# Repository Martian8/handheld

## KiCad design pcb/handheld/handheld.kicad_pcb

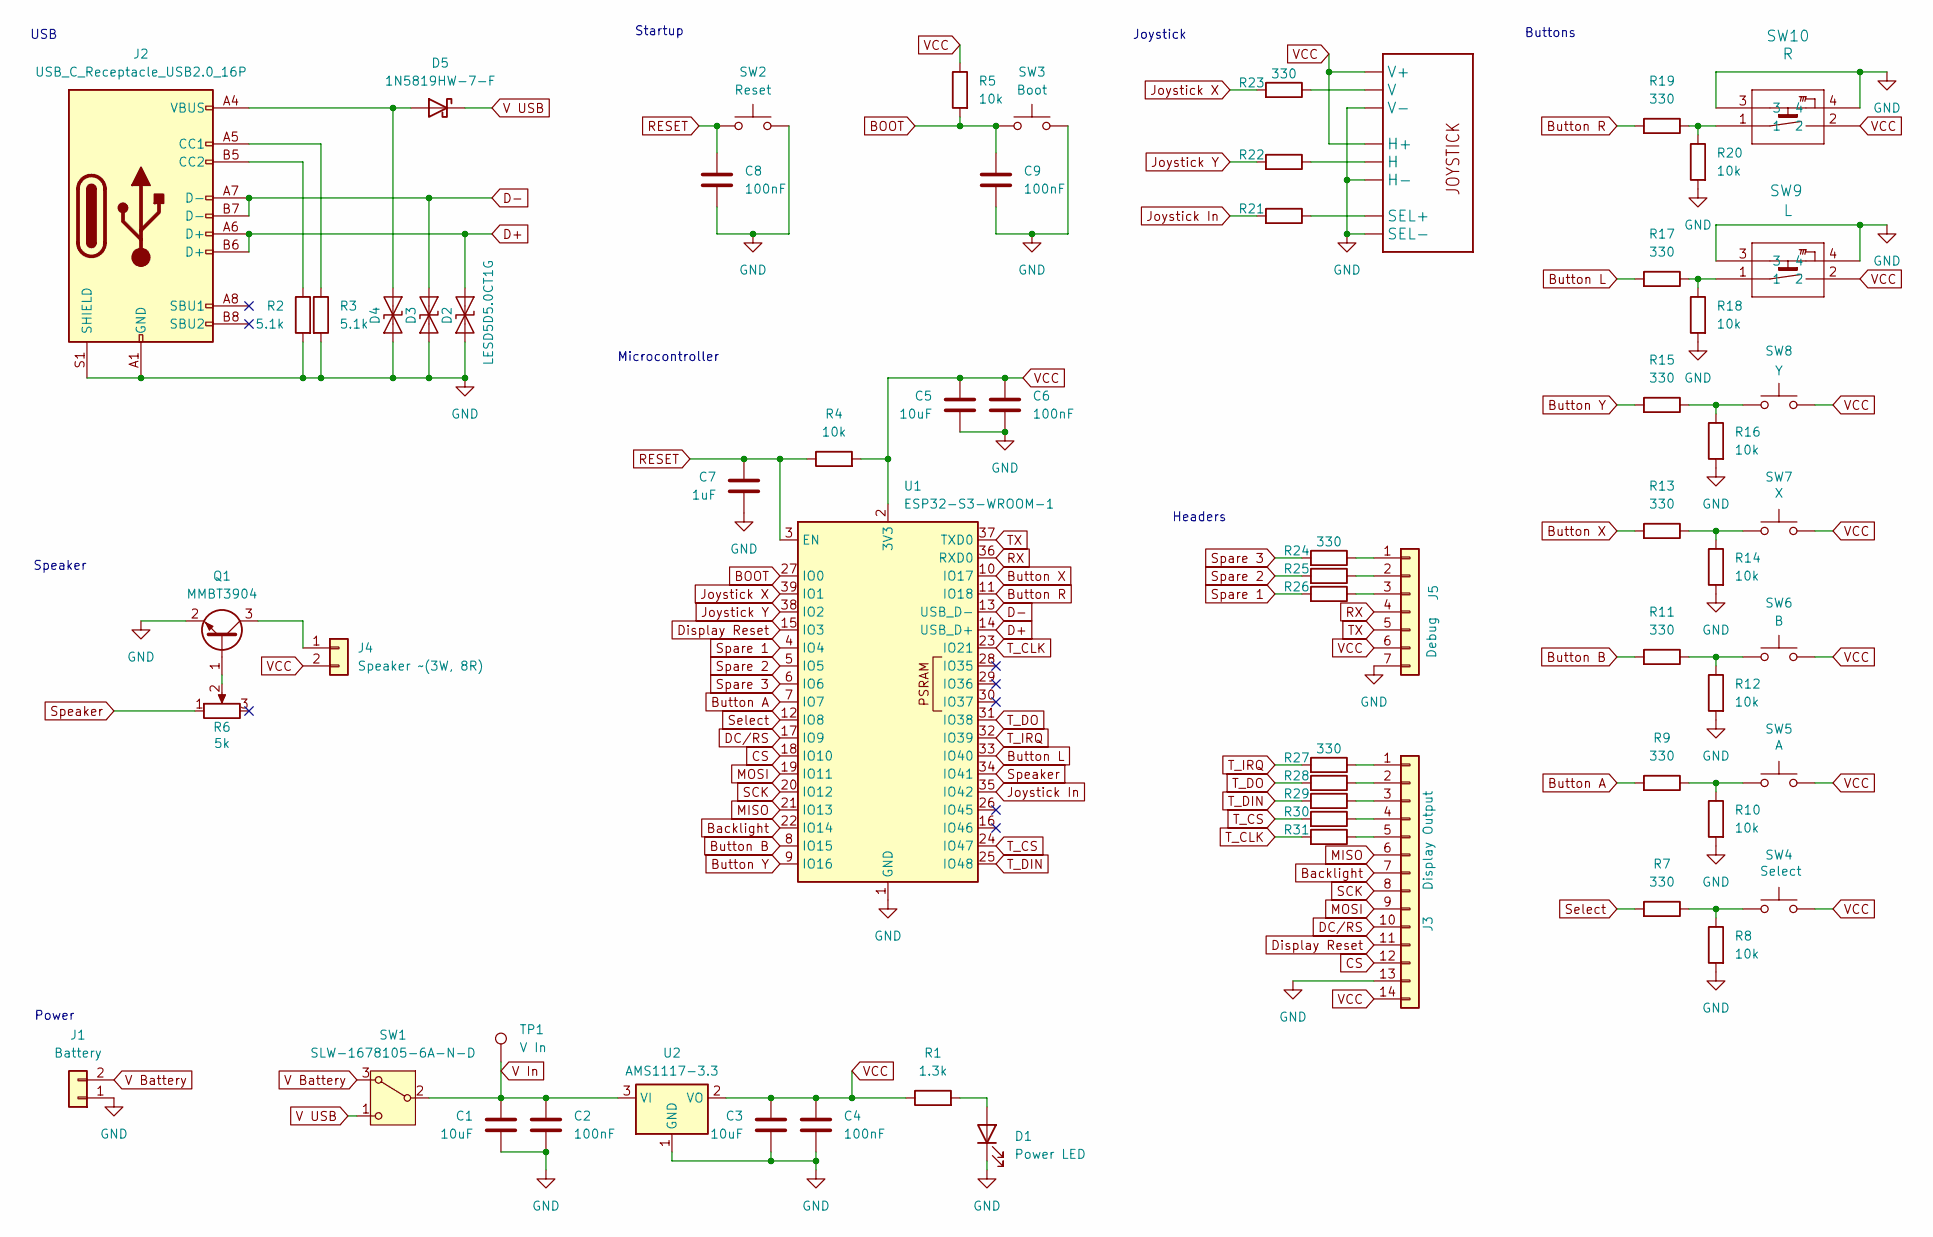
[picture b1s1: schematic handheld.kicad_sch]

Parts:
C1, C3, C5: 10uF; C_0805_2012Metric
C2, C4, C6, C8, C9: 100nF; C_0805_2012Metric
C7: 1uF; C_0805_2012Metric
D1: Power LED; LED_0603_1608Metric
D2, D3, D4: LESD5D5.0CT1G; D_SOD-523
D5: 1N5819HW-7-F; D_SOD-123
J1: Battery; CONN_S2B-PH-K-S_JST
J2: USB_C_Receptacle_USB2.0_16P; USB-SMD_USB-TYPE-C-020
J3: Display Output; PinHeader_1x14_P2.54mm_Horizontal
J4: Speaker ~(3W, 8R); CONN_S2B-PH-K-S_JST
J5: Debug; PinHeader_1x07_P2.54mm_Vertical
Q1: MMBT3904; SOT-23
R1: 1.3k; R_0603_1608Metric
R2, R3: 5.1k; R_0603_1608Metric
R4, R5, R8, R10, R12, R14, R16, R18, R20: 10k; R_0603_1608Metric
R6: 5k; PTV09A-4015F-B104_BRN
R7, R9, R11, R13, R15, R17, R19, R21, R22, R23, R24, R25, R26, R27, R28, R29, R30, R31: 330; R_0603_1608Metric
SW1: SLW-1678105-6A-N-D; SW_SLW-1678105-6A-N-D
SW2: Reset; SW_B3F-1050_OMR
SW3: Boot; SW_B3F-1050_OMR
SW4: Select; SW_B3F-1050_OMR
SW5: A; SW_B3F-1050_OMR
SW6: B; SW_B3F-1050_OMR
SW7: X; SW_B3F-1050_OMR
SW8: Y; SW_B3F-1050_OMR
SW9: L; SW_B3F-3150_OMR
SW10: R; SW_B3F-3150_OMR
TP1: V In; Testpoint
U1: ESP32-S3-WROOM-1
U2: AMS1117-3.3; SOT-223-3_TabPin2
U3: Joystick Mount; JOYSTICK

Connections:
BOOT: C9.1, R5.2, SW3.1, U1.27 (IO0)
Backlight: J3.7, U1.22 (IO14)
Button A: R9.2, U1.7 (IO7)
Button B: R11.2, U1.8 (IO15)
Button L: R17.2, U1.33 (IO40)
Button R: R19.2, U1.11 (IO18)
Button X: R13.2, U1.10 (IO17)
Button Y: R15.2, U1.9 (IO16)
CS: J3.12, U1.18 (IO10)
D+: D2.2 (A2), J2.A6 (D+), J2.B6 (D+), U1.14 (USB_D+)
D-: D3.2 (A2), J2.A7 (D-), J2.B7 (D-), U1.13 (USB_D-)
DC/RS: J3.10, U1.17 (IO9)
Display Reset: J3.11, U1.15 (IO3)
GND: C1.2, C2.2, C3.2, C4.2, C5.2, C6.2, C7.2, C8.2, C9.2, D1.1 (K), D2.1 (A1), D3.1 (A1), D4.1 (A1), J1.1, J2.A1 (GND), J2.A12 (GND), J2.B1 (GND), J2.B12 (GND), J2.S1 (SHIELD), J3.13, J5.7, Q1.2 (E), R2.2, R3.2, R8.2, R10.2, R12.2, R14.2, R16.2, R18.2, R20.2, SW2.2, SW3.2, SW9.3, SW9.4, SW10.3, SW10.4, U1.1 (GND), U1.40 (GND), U1.41 (GND), U2.1 (GND), U3.B2A (SEL-), U3.H3 (H-), U3.V3 (V-)
Joystick In: R21.2, U1.35 (IO42)
Joystick X: R23.2, U1.39 (IO1)
Joystick Y: R22.2, U1.38 (IO2)
MISO: J3.6, U1.21 (IO13)
MOSI: J3.9, U1.19 (IO11)
unnamed: D1.2 (A), R1.2
unnamed: D4.2 (A2), D5.2 (A), J2.A4 (VBUS), J2.A9 (VBUS), J2.B4 (VBUS), J2.B9 (VBUS)
unnamed: J2.A5 (CC1), R3.1
unnamed: J2.B5 (CC2), R2.1
unnamed: J3.1, R27.1
unnamed: J3.2, R28.1
unnamed: J3.3, R29.1
unnamed: J3.4, R30.1
unnamed: J3.5, R31.1
unnamed: J4.1, Q1.3 (C)
unnamed: J5.1, R24.1
unnamed: J5.2, R25.1
unnamed: J5.3, R26.1
unnamed: Q1.1 (B), R6.2
unnamed: R7.1, R8.1, SW4.1
unnamed: R9.1, R10.1, SW5.1
unnamed: R11.1, R12.1, SW6.1
unnamed: R13.1, R14.1, SW7.1
unnamed: R15.1, R16.1, SW8.1
unnamed: R17.1, R18.1, SW9.1
unnamed: R19.1, R20.1, SW10.1
unnamed: R22.1, U3.H2 (H)
unnamed: R21.1, U3.B1A (SEL+)
unnamed: R23.1, U3.V2 (V)
RESET: C7.1, C8.1, R4.1, SW2.1, U1.3 (EN)
RX: J5.4, U1.36 (RXD0)
SCK: J3.8, U1.20 (IO12)
Select: R7.2, U1.12 (IO8)
Spare 1: R26.2, U1.4 (IO4)
Spare 2: R25.2, U1.5 (IO5)
Spare 3: R24.2, U1.6 (IO6)
Speaker: R6.1, U1.34 (IO41)
TX: J5.5, U1.37 (TXD0)
T_CLK: R31.2, U1.23 (IO21)
T_CS: R30.2, U1.24 (IO47)
T_DIN: R29.2, U1.25 (IO48)
T_DO: R28.2, U1.31 (IO38)
T_IRQ: R27.2, U1.32 (IO39)
V Battery: J1.2, SW1.3 (A)
V In: C1.1, C2.1, SW1.2 (B), TP1.1, U2.3 (VI)
V USB: D5.1 (K), SW1.1 (C)
VCC: C3.1, C4.1, C5.1, C6.1, J3.14, J4.2, J5.6, R1.1, R4.2, R5.1, SW4.2, SW5.2, SW6.2, SW7.2, SW8.2, SW9.2, SW10.2, U1.2 (3V3), U2.2 (VO), U3.H1 (H+), U3.V1 (V+)

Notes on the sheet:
Headers
USB
Microcontroller
Power
Startup
Speaker
Joystick
Buttons

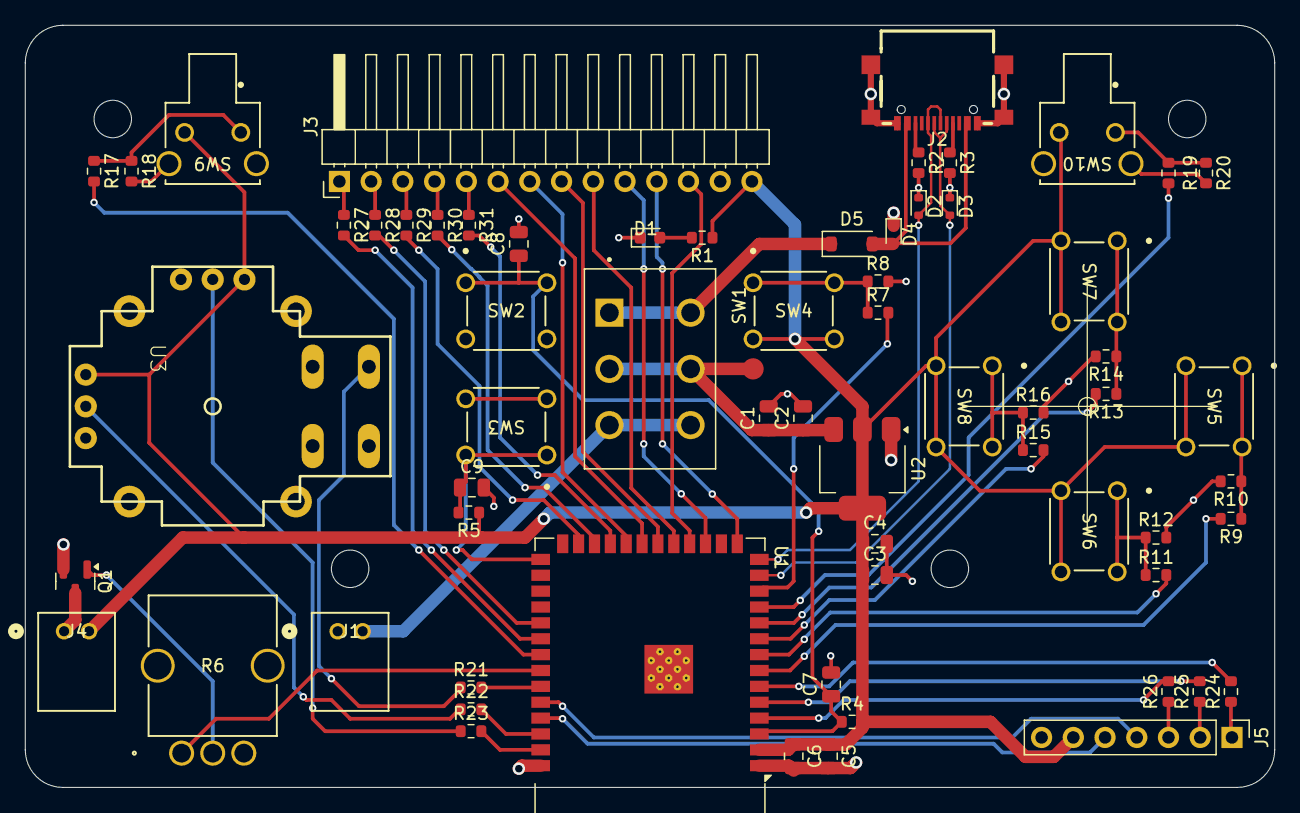
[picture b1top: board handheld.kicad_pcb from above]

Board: 4 copper layers, 100.0 x 61.0 mm, 65 parts (0 on the bottom side), 61 nets.

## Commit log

2025-11-04 initial folders and readme
2025-11-04 Initial empty files
2025-11-04 Picked some components
2025-11-11 Added stuff from website
2025-11-12 Schematic mostly done???
2025-11-17 Assigned pins and finished schematic draft
2025-11-18 Updated symbols and footprints mainly
2025-11-27 Initial PCB routing
2025-12-10 Updated components and shrunk width
2025-12-10 Routed 4 layer design
2025-12-28 Added drill holes and fixed some errors
